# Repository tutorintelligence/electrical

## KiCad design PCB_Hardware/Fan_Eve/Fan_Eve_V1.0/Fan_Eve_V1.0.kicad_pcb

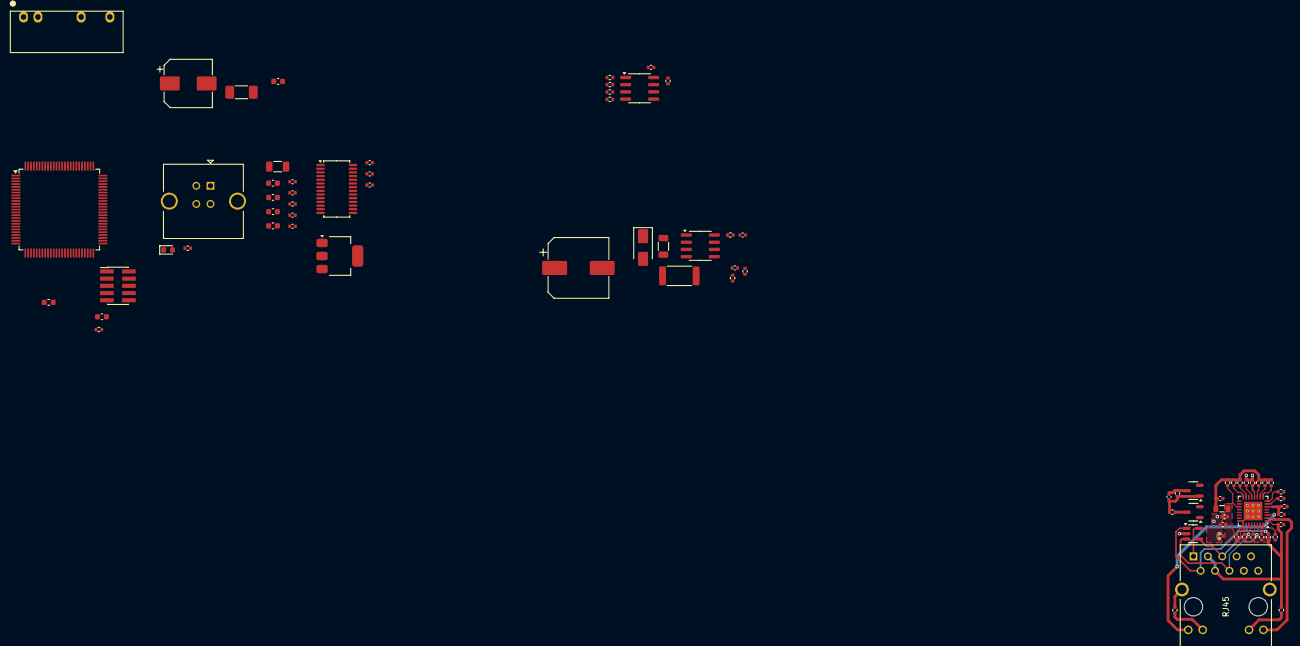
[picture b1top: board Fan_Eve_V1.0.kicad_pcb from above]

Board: 4 copper layers, 78 parts (0 on the bottom side), 56 nets.

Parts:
C1: 4.7u; C_0603_1608Metric
C2, C3, C4, C5, C6, C7, C9, C11, C14, C17, C18, C20, C21, C22, C24, C30, C31: 100n; C_0402_1005Metric
C8, C10: 1u; C_0402_1005Metric
C12, C13, C15, C28: 22u; C_0603_1608Metric
C16: 1n; C_1206_3216Metric
C19: 2.2u; C_0603_1608Metric
C23: 15u; CP_Elec_10x10.5
C25: 10p; C_0402_1005Metric
C26: 470u; CP_Elec_8x10
C27: 1n; C_1808_4520Metric
C29: 10u; C_0402_1005Metric
D2: SS510; D_SMA
D3: LED; LED_0603_1608Metric
FB1: FerriteBead; L_0603_1608Metric
J1: Conn_ARM_JTAG_SWD_10; PinHeader_2x05_P1.27mm_Vertical_SMD
J2: USB_B; USB_B_TE_5787834_Vertical
L1: FB0805/600R/2A; L_0805_2012Metric
Q1: WPM2015-3/TR; SOT-23-3
Q2: LMUN2211LT1G; SOT-23-3
R1, R2, R16, R20: 10k; R_0402_1005Metric
R3: 1k; R_0402_1005Metric
R4, R5, R6, R7: 49.9; R_0402_1005Metric
R8, R9, R10, R11, R12, R13, R14, R15, R17, R18, R30: 2.2k; R_0402_1005Metric
R19: 12.1k; R_0402_1005Metric
R21: 130k; R_0402_1005Metric
R22: 4.42k; R_0402_1005Metric
R23: 180k; R_0402_1005Metric
R24: 24.9k; R_0402_1005Metric
R25: 30m; R_1206_3216Metric
R26: 4.7k; R_2512_6332Metric
R27: 4.7; R_0402_1005Metric
R28: 56.2k; R_0402_1005Metric
R29: 10.5k; R_0402_1005Metric
RJ1: HY931147C
U1: STM32H743VITx; LQFP-100_14x14mm_P0.5mm
U2: LAN8710A-EZC; QFN-32-1EP_5x5mm_P0.5mm_EP3.3x3.3mm_ThermalVias
U3: ESDS314DBVR; SOT-23-5
U4: TPS2376D; SOIC-8_3.9x4.9mm_P1.27mm
U5: TX4138; SOIC-8_3.9x4.9mm_P1.27mm
U6: F0505S-2WR2
U7: AMS1117-3.3; SOT-223-3_TabPin2
U8: PCA9685PW; TSSOP-28_4.4x9.7mm_P0.65mm

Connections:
+3.3V: C1.1, C2.1, C3.1, C4.1, C5.1, C6.1, C7.1, C10.1, C12.1, FB1.2, J1.1 (VTref), Q1.3 (D), R2.1, U1.6 (VBAT), U1.11 (VDD), U1.27 (VDD), U1.50 (VDD), U1.75 (VDD), U1.100 (VDD)
+3.3VA: C8.1, C9.1, FB1.1, U1.21 (VDDA)
+3.3VLAN: C13.1, C14.1, L1.1, Q1.2 (S), R8.2, R9.2, R10.2, R14.2, R15.2, R16.2, U2.12 (VDDIO)
+5V: C28.2, C29.1, C30.1, U6.5 (0V), U8.1 (A0), U8.3 (A2), U8.5 (A4), U8.28 (VDD)
+5V USB: D3.2 (A), J2.1 (VBUS)
/Ethernet/ETHGREEN: RJ1.P$14 (G-), U2.2 (LED2/~INTSEL)
/Ethernet/ETHYELLOW: RJ1.P$11 (Y+), U2.3 (LED1/~REGOFF)
/Ethernet/ETH_CRS_DV: R14.1, U1.31 (PA7), U2.15 (COL/CRS_DV/~MODE2)
/Ethernet/ETH_MDC: U1.16 (PC1), U2.17 (MDC)
/Ethernet/ETH_MDIO: R15.1, U1.24 (PA2), U2.16 (MDIO)
/Ethernet/ETH_REF_CLK: U1.23 (PA1), U2.5 (XTAL1/CLKIN)
/Ethernet/ETH_RXD0: R8.1, U1.32 (PC4), U2.11 (RXD0/~MODE0)
/Ethernet/ETH_RXD1: R9.1, U1.33 (PC5), U2.10 (RXD1/~MODE1)
/Ethernet/ETH_TXD0: U1.51 (PB12), U2.22 (TXD0)
/Ethernet/ETH_TXD1: U1.52 (PB13), U2.23 (TXD1)
/Ethernet/ETH_TX_EN: U1.47 (PB11), U2.21 (TXEN)
/Ethernet/V+: C22.1, C23.1, R21.1, R24.1, R25.1, R26.1, RJ1.P$9 (V+), U4.8 (VDD), U5.3 (VIN)
/Ethernet/V-: C22.2, R20.1, R22.1, R23.1, RJ1.P$10 (V-), U4.4 (VSS)
/MCU/NRST: C11.1, U1.14 (NRST)
/MCU/SWCLK: J1.4 (SWCLK/TCK), U1.76 (PA14)
/MCU/SWDIO: J1.2 (SWDIO/TMS), U1.72 (PA13)
/MCU/SWO: J1.6 (SWO/TDO), U1.89 (PB3)
/MCU/USB_D+: J2.3 (D+), U1.71 (PA12)
/MCU/USB_D-: J2.2 (D-), U1.70 (PA11)
/POE/ILIM: R25.2, U5.2 (ILIM_1)
/POE/POE_EN: U4.6 (PG), U5.6 (EN)
GND: C1.2, C2.2, C3.2, C4.2, C5.2, C6.2, C7.2, C8.2, C9.2, C10.2, C11.2, C13.2, C14.2, C15.2, C16.2, C17.2, C18.2, C19.1, C20.1, C21.1, C27.1, C28.1, C29.2, C30.2, C31.2, J1.3 (GND), J1.5 (GND), J1.9 (GNDDetect), J2.4 (GND), J2.5 (Shield), Q2.2 (E), R1.2, R11.1, R12.1, R13.1, R18.2, R19.1, R30.2, RJ1.GND1, RJ1.GND2, U1.10 (VSS), U1.19 (VSSA), U1.26 (VSS), U1.49 (VSS), U1.74 (VSS), U1.99 (VSS), U2.24 (TXD2), U2.25 (TXD3), U2.33 (VSS), U3.2 (GND), U6.7 (+Vo), U8.2 (A1), U8.4 (A3), U8.14 (VSS), U8.24 (A5)
GNDPWR: C23.2, C26.2, C27.2, D2.2 (A), R26.2, R29.1, U4.5 (RTN), U5.4 (GND), U6.2 (GND)
unnamed: C24.1, R27.2
unnamed: C24.2, D2.1 (K), U5.1 (SW)
unnamed: D3.1 (K), R30.1
unnamed: C12.2, Q1.1 (G), R2.2, R3.1
unnamed: Q2.3 (C), R3.2
unnamed: R17.1, RJ1.P$13 (G+)
unnamed: R7.2, RJ1.P$1 (RX+), U2.30 (RXN), U3.5 (I/O4)
unnamed: R6.2, RJ1.P$2 (RX-), U2.31 (RXP), U3.1 (I/O1)
unnamed: C15.1, C16.1, C17.1, C18.1, C21.2, L1.2, R4.1, R5.1, R6.1, R7.1, R17.2, RJ1.P$3 (RXCT), RJ1.P$4 (TXCT), U2.1 (VDD2A), U2.27 (VDD1A)
unnamed: R5.2, RJ1.P$5 (TX+), U2.28 (TXN), U3.4 (I/O3)
unnamed: R4.2, RJ1.P$6 (TX-), U2.29 (TXP), U3.3 (I/O2)
unnamed: R18.1, RJ1.P$12 (Y-)
unnamed: R1.1, U1.94 (BOOT0)
unnamed: R19.2, U2.32 (RBIAS)
unnamed: R12.2, U2.7 (RXCLK/~PHYAD1)
unnamed: R10.1, U2.9 (RXD2/~RMIISEL)
unnamed: R11.2, U2.8 (RXD3/~PHYAD2)
unnamed: R13.2, U2.13 (RXER/RXD4/~PHYAD0)
unnamed: C19.2, C20.2, U2.6 (VDDCR)
unnamed: R16.1, U2.19 (~RST)
unnamed: R22.2, U4.2 (CLASS)
unnamed: R24.2, U4.3 (DET)
unnamed: R23.2, U4.1 (ILIM)
unnamed: R20.2, R21.2, U4.7 (UVLO)
unnamed: R27.1, U5.8 (BS)
unnamed: C25.1, R28.1, R29.2, U5.5 (FB)
unnamed: C25.2, C26.1, R28.2, U6.1 (Vin)
unnamed: C31.1, U8.25 (EXTCLK)

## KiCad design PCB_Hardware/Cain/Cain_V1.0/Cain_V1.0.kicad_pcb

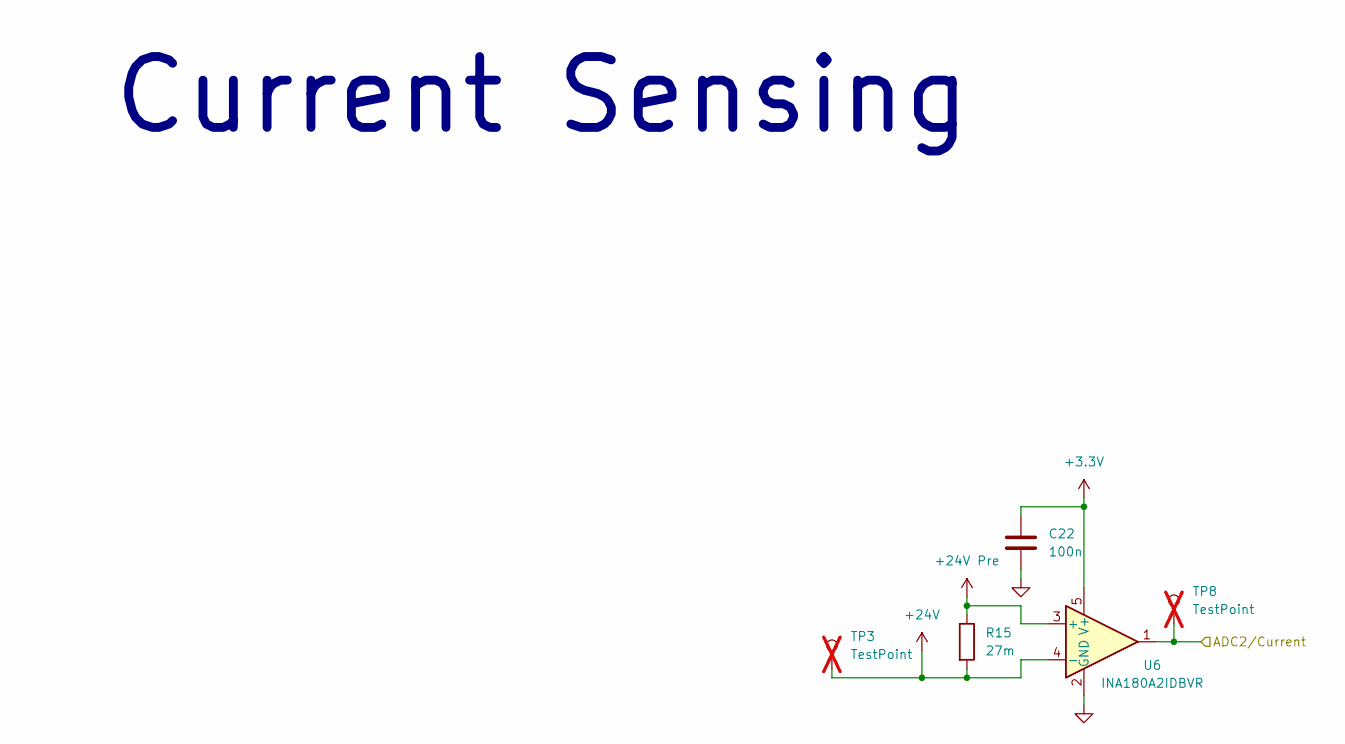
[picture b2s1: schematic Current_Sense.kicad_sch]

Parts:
C22: 100n; C_0402_1005Metric; JLCPCB Part Number C1525
R15: 27m; R_1206_3216Metric; JLCPCB Part Number C2988658
TP3, TP8: TestPoint; TestPoint_Pad_D1.0mm; not fitted
U6: INA180A2IDBVR; SOT-23-5; JLCPCB Part Number C192764

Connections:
+3.3V: C22.1, U6.5 (V+); also elsewhere on the board
+24V: R15.2, TP3.1, U6.4 (-); also elsewhere on the board
+24V Pre: R15.1, U6.3 (+); also elsewhere on the board
/Current Sense/ADC2/Current: TP8.1, U6.1; also elsewhere on the board
GND: C22.2, U6.2 (GND); also elsewhere on the board

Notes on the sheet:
Current Sensing

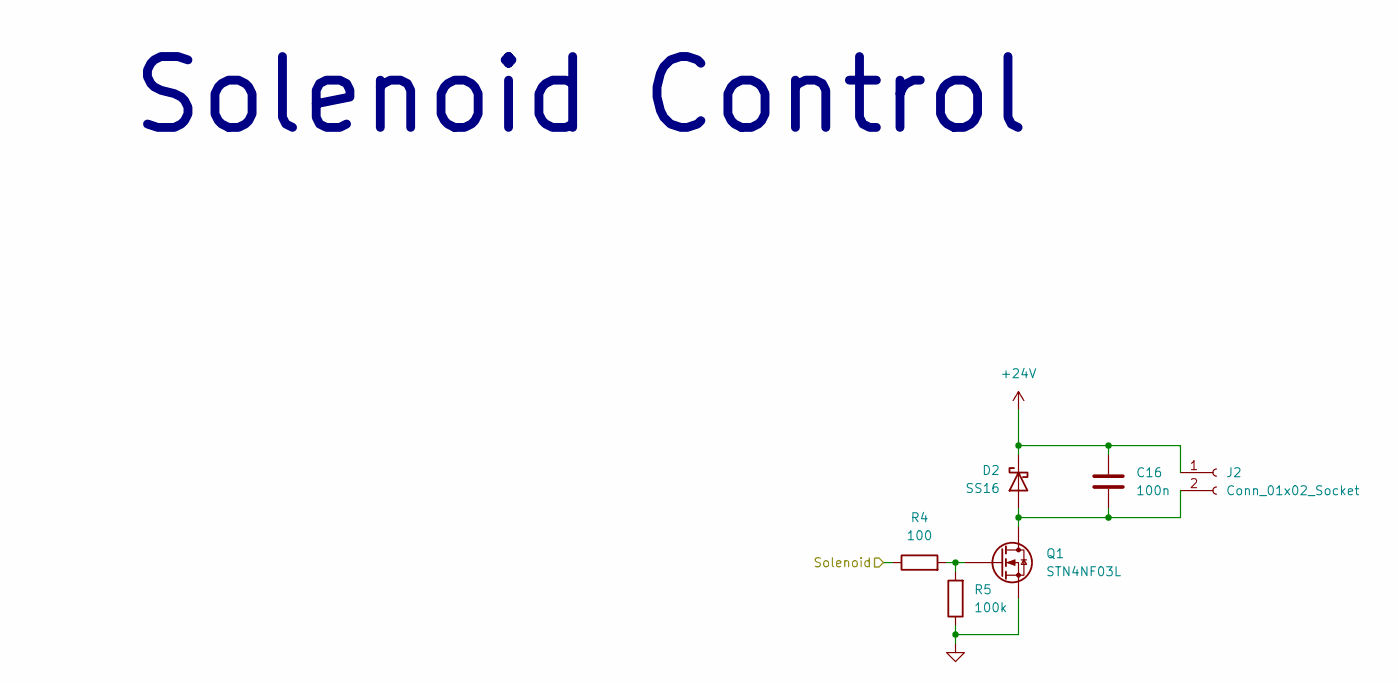
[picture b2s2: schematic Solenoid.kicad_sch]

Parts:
C16: 100n; C_0603_1608Metric; JLCPCB Part Number C1591
D2: SS16; D_SMA; JLCPCB Part Number C557917
J2: Conn_01x02_Socket; JST_XH_B2B-XH-A_1x02_P2.50mm_Vertical; JLCPCB Part Number C158012
Q1: STN4NF03L; SOT-223-3_TabPin2; JLCPCB Part Number C85568
R4: 100; R_0402_1005Metric; JLCPCB Part Number C25076
R5: 100k; R_0402_1005Metric; JLCPCB Part Number C25741

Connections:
+24V: C16.1, D2.1 (K), J2.1; also elsewhere on the board
/MCU/Solenoid: R4.1; also elsewhere on the board
GND: Q1.3 (S), R5.1; also elsewhere on the board
unnamed: C16.2, D2.2 (A), J2.2, Q1.2 (D)
unnamed: Q1.1 (G), R4.2, R5.2

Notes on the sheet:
Solenoid Control

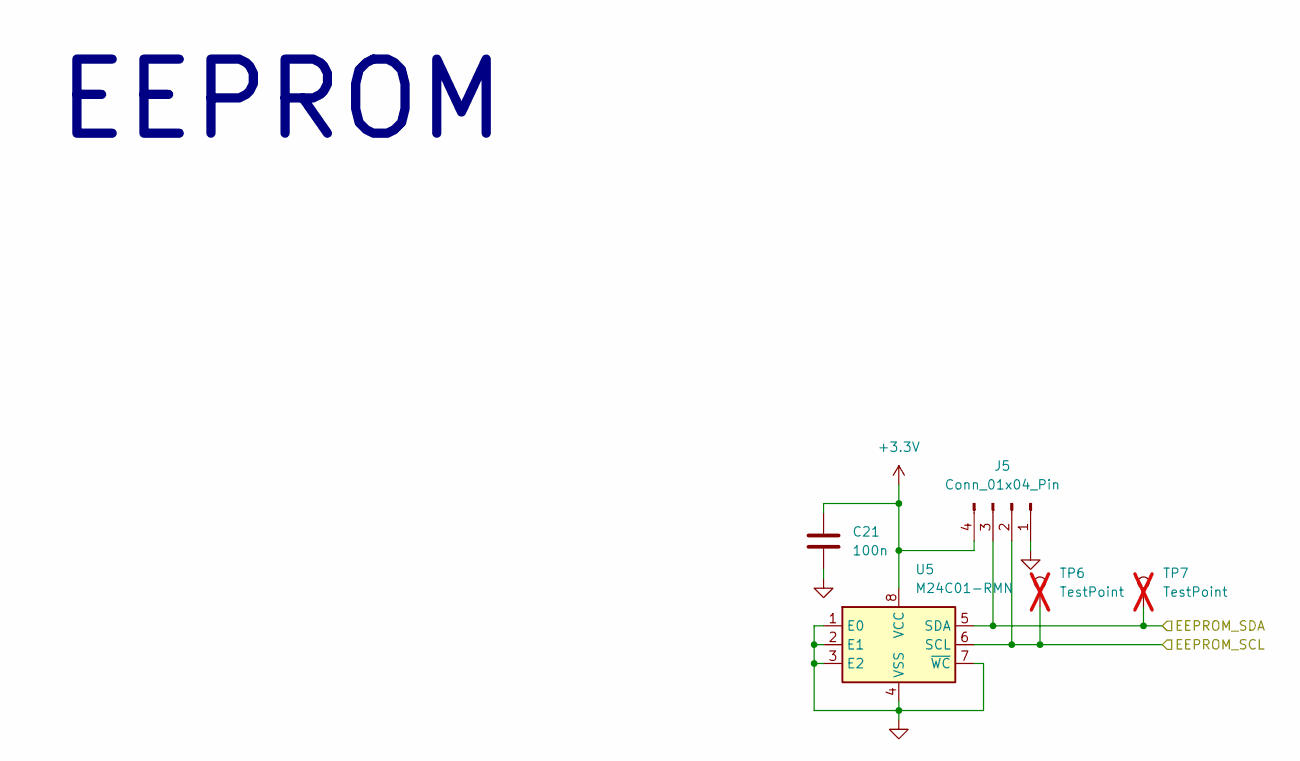
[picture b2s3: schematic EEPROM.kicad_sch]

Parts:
C21: 100n; C_0402_1005Metric; JLCPCB Part Number C1525
J5: Conn_01x04_Pin; PinHeader_1x04_P1.00mm_Vertical; JLCPCB Part Number C37328854
TP6, TP7: TestPoint; TestPoint_Pad_D1.0mm; not fitted
U5: M24C01-RMN; SOIC-8_3.9x4.9mm_P1.27mm; JLCPCB Part Number C146163

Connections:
+3.3V: C21.1, J5.4, U5.8 (VCC); also elsewhere on the board
/EEPROM/EEPROM_SCL: J5.2, TP6.1, U5.6 (SCL); also elsewhere on the board
/EEPROM/EEPROM_SDA: J5.3, TP7.1, U5.5 (SDA); also elsewhere on the board
GND: C21.2, J5.1, U5.1 (E0), U5.2 (E1), U5.3 (E2), U5.4 (VSS), U5.7 (~WC); also elsewhere on the board

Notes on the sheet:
EEPROM

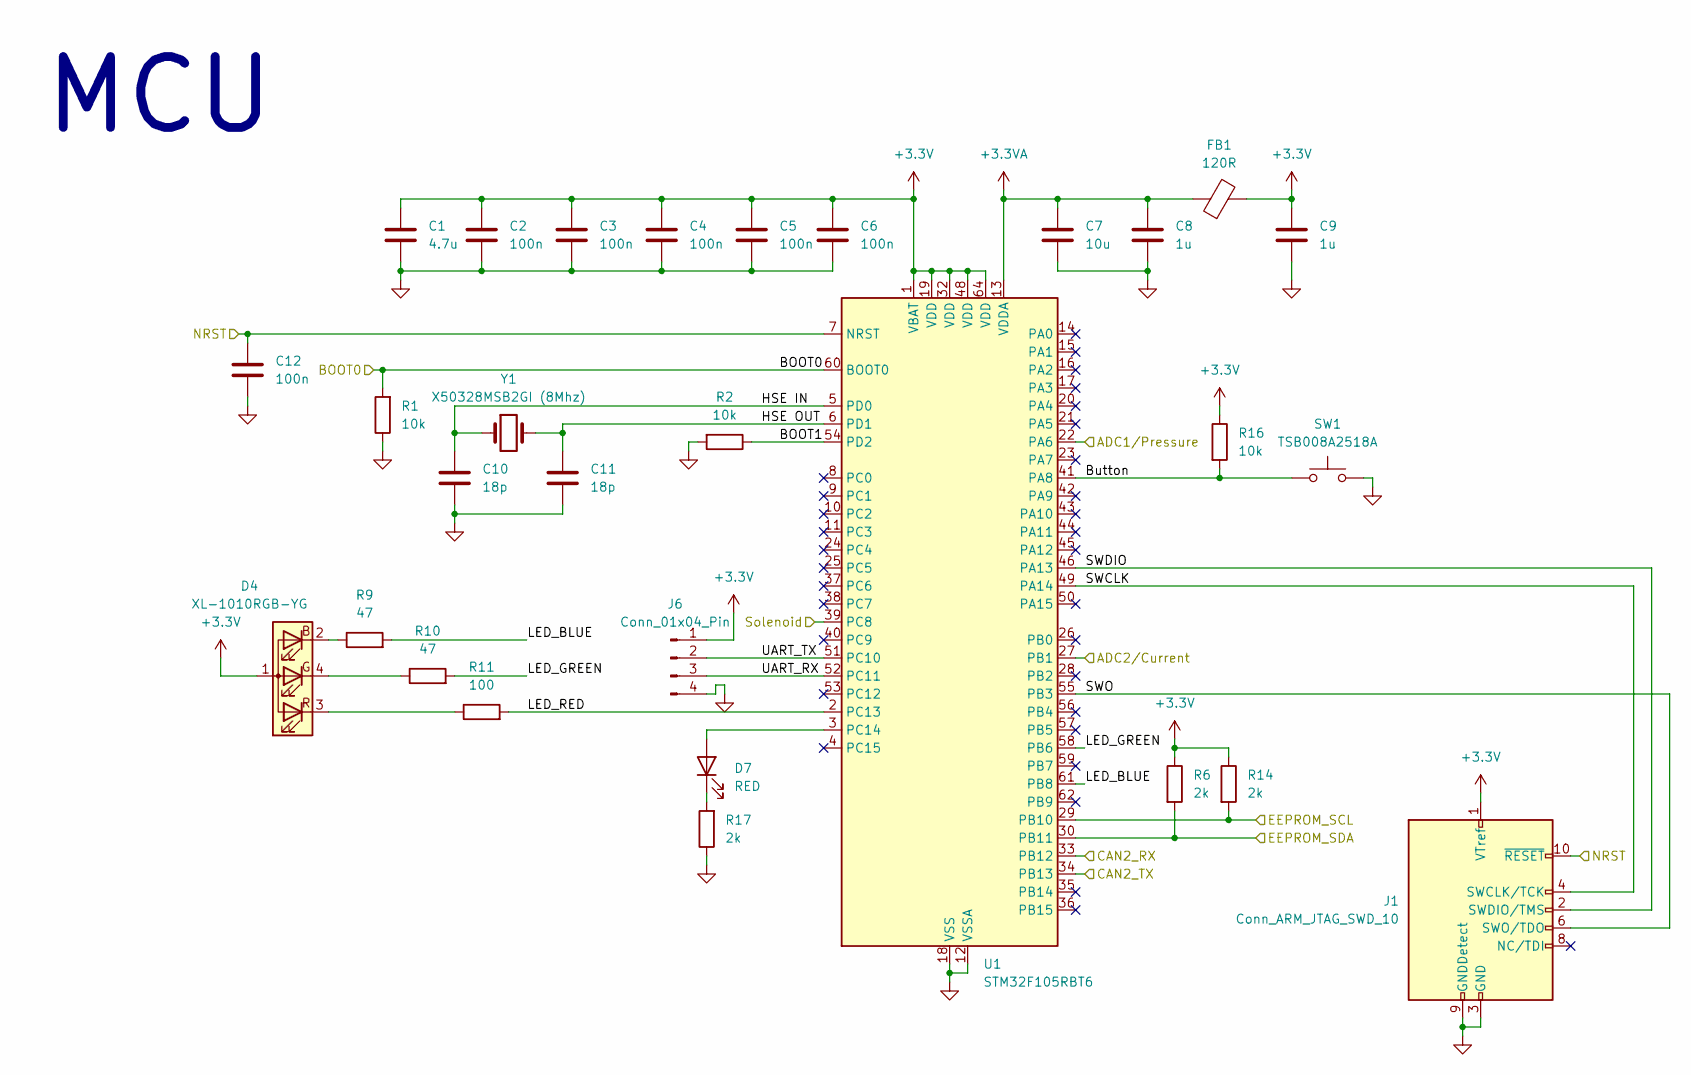
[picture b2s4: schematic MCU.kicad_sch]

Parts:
C1: 4.7u; C_0603_1608Metric; JLCPCB Part Number C19666
C2, C3, C4, C5, C6, C12: 100n; C_0402_1005Metric; JLCPCB Part Number C1525
C7: 10u; C_0402_1005Metric; JLCPCB Part Number C15525
C8, C9: 1u; C_0402_1005Metric; JLCPCB Part Number C1525
C10, C11: 18p; C_0402_1005Metric; JLCPCB Part Number C52923
D4: XL-1010RGB-YG; LED_01x01; JLCPCB Part Number C965834
D7: RED; LED_0603_1608Metric; JLCPCB Part Number C434419
FB1: 120R; L_0603_1608Metric; JLCPCB Part Number C113030
J1: Conn_ARM_JTAG_SWD_10; PinHeader_2x05_P1.27mm_Vertical; JLCPCB Part Number C2935953
J6: Conn_01x04_Pin; PinHeader_1x04_P1.00mm_Vertical; JLCPCB Part Number C37328854
R1, R2, R16: 10k; R_0402_1005Metric; JLCPCB Part Number C25744
R6, R14, R17: 2k; R_0402_1005Metric; JLCPCB Part Number C4109
R9, R10: 47; R_0402_1005Metric; JLCPCB Part Number C1211
R11: 100; R_0402_1005Metric; JLCPCB Part Number C25076
SW1: TSB008A2518A; JLCPCB Part Number C2888455
U1: STM32F105RBT6; LQFP-64_10x10mm_P0.5mm; JLCPCB Part Number C8349
Y1: X50328MSB2GI (8Mhz); Crystal_SMD_5032-2Pin_5.0x3.2mm; JLCPCB Part Number C115962

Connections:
+3.3V: C1.1, C2.1, C3.1, C4.1, C5.1, C6.1, C9.1, D4.1 (A), FB1.2, J1.1 (VTref), J6.1, R6.1, R14.1, R16.1, U1.1 (VBAT), U1.19 (VDD), U1.32 (VDD), U1.48 (VDD), U1.64 (VDD); also elsewhere on the board
+3.3VA: C7.1, C8.1, FB1.1, U1.13 (VDDA); also elsewhere on the board
/CAN2.0/Power/CAN2_RX: U1.33 (PB12); also elsewhere on the board
/CAN2.0/Power/CAN2_TX: U1.34 (PB13); also elsewhere on the board
/CAN2.0/Power/NRST: C12.1, J1.10 (~RESET), U1.7 (NRST); also elsewhere on the board
/Current Sense/ADC2/Current: U1.27 (PB1); also elsewhere on the board
/EEPROM/EEPROM_SCL: R14.2, U1.29 (PB10); also elsewhere on the board
/EEPROM/EEPROM_SDA: R6.2, U1.30 (PB11); also elsewhere on the board
/MCU/ADC1/Pressure: U1.22 (PA6); also elsewhere on the board
/MCU/BOOT0: R1.2, U1.60 (BOOT0); also elsewhere on the board
/MCU/BOOT1: R2.1, U1.54 (PD2)
/MCU/Button: R16.2, SW1.1, U1.41 (PA8)
/MCU/HSE IN: C10.1, U1.5 (PD0), Y1.1
/MCU/HSE OUT: C11.1, U1.6 (PD1), Y1.2
/MCU/LED_BLUE: R9.2, U1.61 (PB8)
/MCU/LED_GREEN: R10.2, U1.58 (PB6)
/MCU/LED_RED: R11.2, U1.2 (PC13)
/MCU/SWCLK: J1.4 (SWCLK/TCK), U1.49 (PA14)
/MCU/SWDIO: J1.2 (SWDIO/TMS), U1.46 (PA13)
/MCU/SWO: J1.6 (SWO/TDO), U1.55 (PB3)
/MCU/Solenoid: U1.39 (PC8); also elsewhere on the board
/MCU/UART_RX: J6.3, U1.52 (PC11)
/MCU/UART_TX: J6.2, U1.51 (PC10)
GND: C1.2, C2.2, C3.2, C4.2, C5.2, C6.2, C7.2, C8.2, C9.2, C10.2, C11.2, C12.2, J1.3 (GND), J1.5 (GND), J1.9 (GNDDetect), J6.4, R1.1, R2.2, R17.1, SW1.2, U1.12 (VSSA), U1.18 (VSS), U1.31 (VSS), U1.47 (VSS), U1.63 (VSS); also elsewhere on the board
unnamed: D4.2 (BK), R9.1
unnamed: D4.4 (GK), R10.1
unnamed: D4.3 (RK), R11.1
unnamed: D7.2 (A), U1.3 (PC14)
unnamed: D7.1 (K), R17.2

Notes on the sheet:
MCU

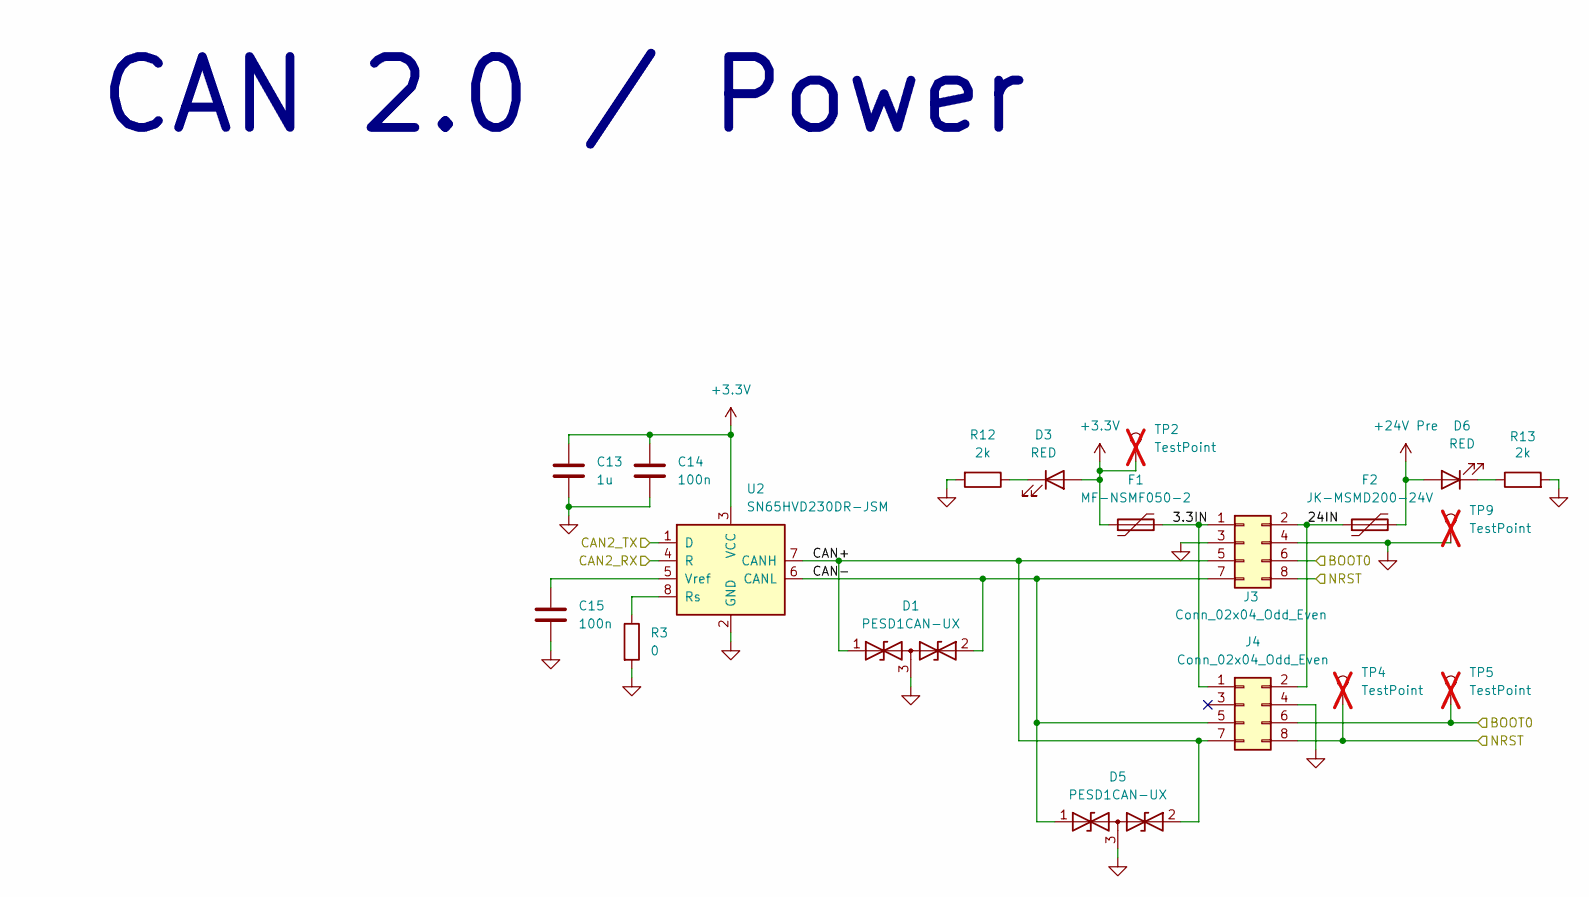
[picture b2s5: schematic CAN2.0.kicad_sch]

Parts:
C13: 1u; C_0402_1005Metric; JLCPCB Part Number C1525
C14, C15: 100n; C_0402_1005Metric; JLCPCB Part Number C1525
D1, D5: PESD1CAN-UX; SOT-323_SC-70; JLCPCB Part Number C152727
D3, D6: RED; LED_0603_1608Metric; JLCPCB Part Number C434419
F1: MF-NSMF050-2; Fuse_1210_3225Metric; JLCPCB Part Number C75464
F2: JK-MSMD200-24V; Fuse_1812_4532Metric; JLCPCB Part Number C561584
J3, J4: Conn_02x04_Odd_Even; CONN_B8B-PHDSS_JST; JLCPCB Part Number C157975
R3: 0; R_0402_1005Metric; JLCPCB Part Number C1091
R12, R13: 2k; R_0402_1005Metric; JLCPCB Part Number C4109
TP2, TP4, TP5, TP9: TestPoint; TestPoint_Pad_D1.0mm; not fitted
U2: SN65HVD230DR-JSM; SOIC-8_3.9x4.9mm_P1.27mm; JLCPCB Part Number C46596299

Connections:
+3.3V: C13.1, C14.1, D3.2 (A), F1.1, TP2.1, U2.3 (VCC); also elsewhere on the board
+24V Pre: D6.2 (A), F2.2; also elsewhere on the board
/CAN2.0/Power/3.3IN: F1.2, J3.1, J4.1
/CAN2.0/Power/24IN: F2.1, J3.2, J4.2
/CAN2.0/Power/CAN2_RX: U2.4 (R); also elsewhere on the board
/CAN2.0/Power/CAN2_TX: U2.1 (D); also elsewhere on the board
/CAN2.0/Power/CAN+: D1.1 (A1), D5.2 (A2), J3.5, J4.7, U2.7 (CANH)
/CAN2.0/Power/CAN-: D1.2 (A2), D5.1 (A1), J3.7, J4.5, U2.6 (CANL)
/CAN2.0/Power/NRST: J3.8, J4.8, TP4.1; also elsewhere on the board
/MCU/BOOT0: J3.6, J4.6, TP5.1; also elsewhere on the board
GND: C13.2, C14.2, C15.2, D1.3 (common), D5.3 (common), J3.3, J3.4, J4.4, R3.2, R12.2, R13.2, TP9.1, U2.2 (GND); also elsewhere on the board
unnamed: D3.1 (K), R12.1
unnamed: D6.1 (K), R13.1
unnamed: R3.1, U2.8 (Rs)
unnamed: C15.1, U2.5 (Vref)

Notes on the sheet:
CAN 2.0 / Power

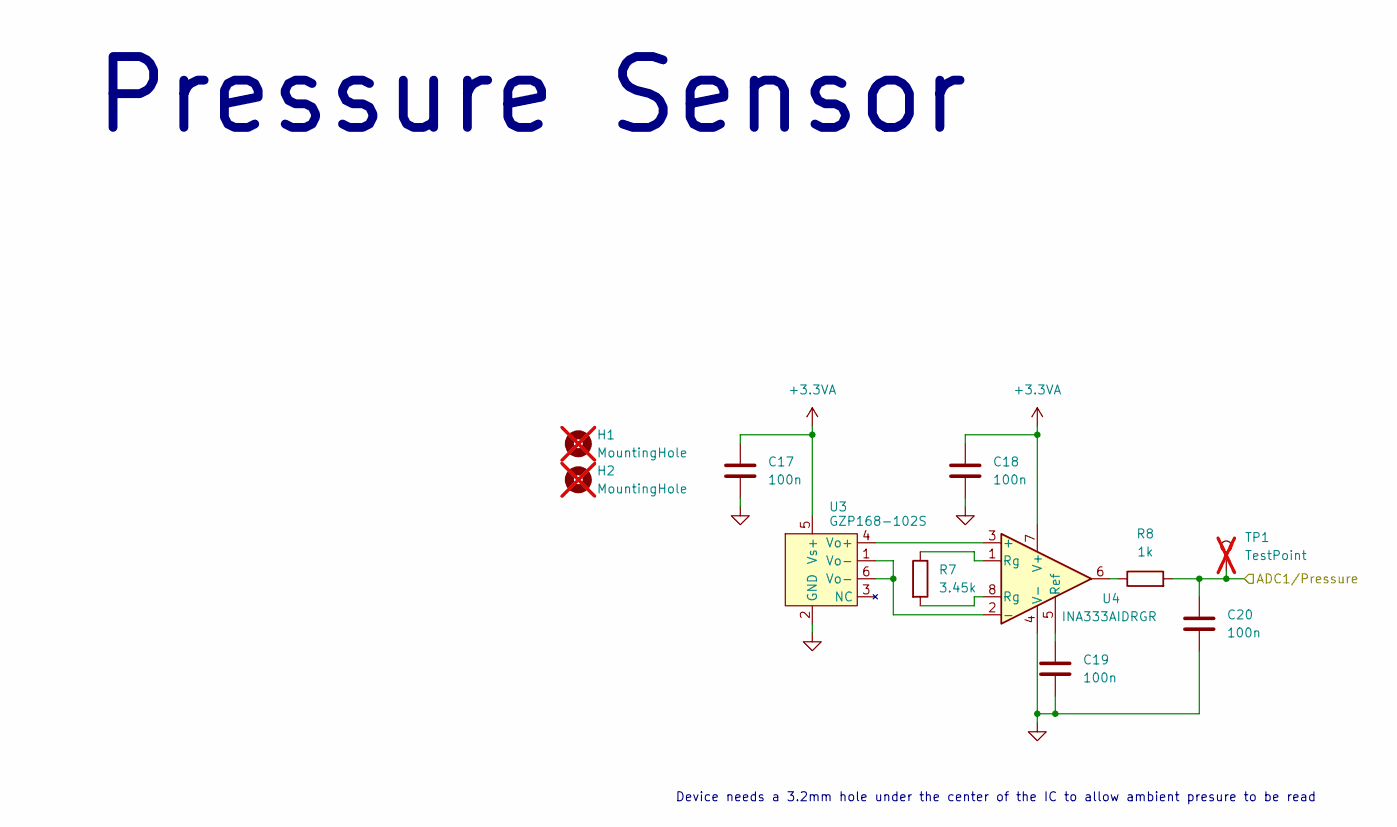
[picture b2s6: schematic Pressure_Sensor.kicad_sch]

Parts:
C17, C18, C19, C20: 100n; C_0402_1005Metric; JLCPCB Part Number C1525
H1, H2: MountingHole; MountingHole_3.2mm_M3; not fitted
R7: 3.45k; R_0402_1005Metric; JLCPCB Part Number C4940
R8: 1k; R_0402_1005Metric; JLCPCB Part Number C11702
TP1: TestPoint; TestPoint_Pad_D1.0mm; not fitted
U3: GZP168-102S; JLCPCB Part Number C3037990
U4: INA333AIDRGR; VSSOP-8_3x3mm_P0.65mm; JLCPCB Part Number C2057429

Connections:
+3.3VA: C17.1, C18.1, U3.5 (Vs+), U4.7 (V+); also elsewhere on the board
/MCU/ADC1/Pressure: C20.1, R8.2, TP1.1; also elsewhere on the board
GND: C17.2, C18.2, C19.2, C20.2, U3.2 (GND), U4.4 (V-); also elsewhere on the board
unnamed: R7.1, U4.1 (Rg)
unnamed: R7.2, U4.8 (Rg)
unnamed: R8.1, U4.6
unnamed: U3.4 (Vo+), U4.3 (+)
unnamed: U3.1 (Vo-), U3.6 (Vo-), U4.2 (-)
unnamed: C19.1, U4.5 (Ref)

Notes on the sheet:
Device needs a 3.2mm hole under the center of the IC to allow ambient presure to be read
Pressure Sensor

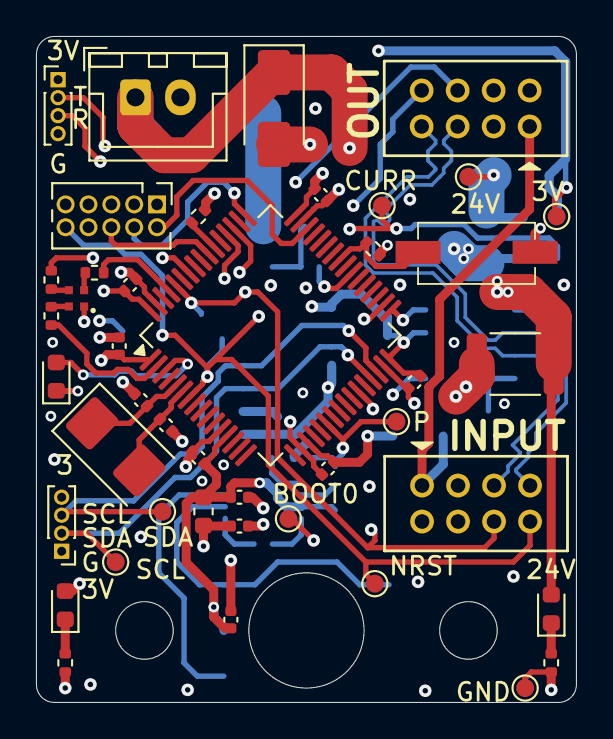
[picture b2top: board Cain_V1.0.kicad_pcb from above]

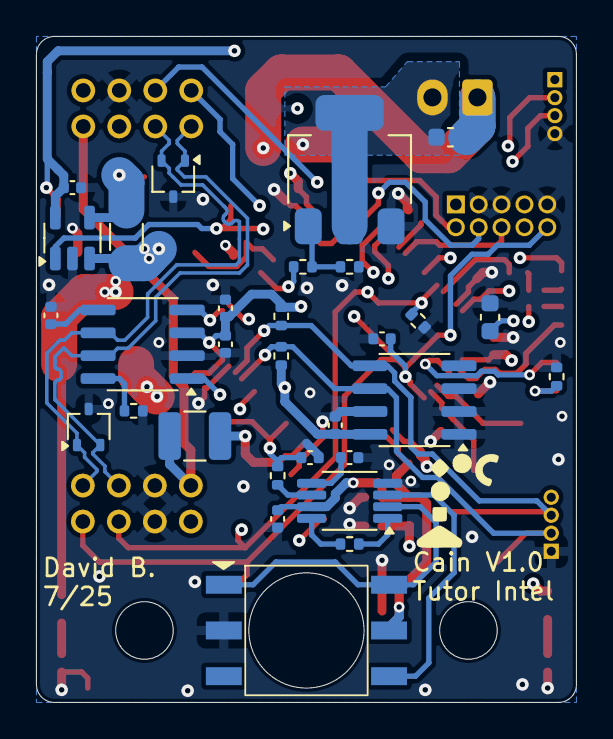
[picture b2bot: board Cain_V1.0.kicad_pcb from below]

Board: 4 copper layers, 30.0 x 37.0 mm, 75 parts (30 on the bottom side), 47 nets.

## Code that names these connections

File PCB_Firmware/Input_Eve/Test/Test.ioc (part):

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Mcu.Name=STM32H743ZITx
Mcu.Package=LQFP144
Mcu.UserName=STM32H743ZITx
PA1.Mode=RMII
PA1.Signal=ETH_REF_CLK
PA10.Signal=S_TIM1_CH3
PA11.Mode=Device_Only
PA11.Signal=USB_OTG_FS_DM
PA12.Mode=Device_Only
PA12.Signal=USB_OTG_FS_DP
PA13\ (JTMS/SWDIO).Mode=Trace_Asynchronous_SW
PA13\ (JTMS/SWDIO).Signal=DEBUG_JTMS-SWDIO
PA14\ (JTCK/SWCLK).Mode=Trace_Asynchronous_SW
PA14\ (JTCK/SWCLK).Signal=DEBUG_JTCK-SWCLK
PA15\ (JTDI).Mode=Hardware Flow Control (RS485)
PA15\ (JTDI).Signal=UART4_DE
PA2.Mode=RMII
PA2.Signal=ETH_MDIO
PA3.Signal=ADCx_INP15
PA4.Signal=ADCx_INP18
PA5.Signal=ADCx_INP19
PA6.Signal=ADCx_INP3
PA7.Mode=RMII
PA7.Signal=ETH_CRS_DV
PA8.Signal=S_TIM1_CH1
PA9.Mode=Activate_VBUS
PA9.Signal=USB_OTG_FS_VBUS
PB0.Signal=ADCx_INP9
PB1.Signal=ADCx_INP5
PB10.Signal=S_TIM2_CH3
PB11.Mode=RMII
PB11.Signal=ETH_TX_EN
PB12.GPIOParameters=GPIO_Label
PB12.GPIO_Label=USB_FAULT
PB12.Signal=GPIO_Input
PB13.Mode=Activate_VBUS_FS
PB13.Signal=USB_OTG_HS_VBUS
PB14.Mode=Host_FS
PB14.Signal=USB_OTG_HS_DM
PB15.Mode=Host_FS
PB15.Signal=USB_OTG_HS_DP
PB2.Mode=Single Bank 2
PB2.Signal=QUADSPI_CLK
PB3\ (JTDO/TRACESWO).Mode=Trace_Asynchronous_SW
PB3\ (JTDO/TRACESWO).Signal=DEBUG_JTDO-SWO
PB4\ (NJTRST).Signal=S_TIM3_CH1
PB5.Signal=S_TIM3_CH2
PB6.Signal=S_TIM4_CH1
PB7.Signal=S_TIM4_CH2
PB8.Signal=S_TIM4_CH3
PB9.Signal=S_TIM4_CH4
PC0.Signal=ADCx_INP10
PC1.Mode=RMII
PC1.Signal=ETH_MDC
PC10.GPIOParameters=GPIO_Label
PC10.GPIO_Label=RS485_TX
PC10.Mode=Asynchronous
PC10.Signal=UART4_TX
PC11.Mode=Single Bank 2
PC11.Signal=QUADSPI_BK2_NCS
PC12.GPIOParameters=GPIO_Label
PC12.GPIO_Label=RS232_TX_1
PC12.Mode=Asynchronous
PC12.Signal=UART5_TX
PC14-OSC32_IN\ (OSC32_IN).Mode=LSE-External-Oscillator
PC14-OSC32_IN\ (OSC32_IN).Signal=RCC_OSC32_IN
PC15-OSC32_OUT\ (OSC32_OUT).Mode=LSE-External-Oscillator
PC15-OSC32_OUT\ (OSC32_OUT).Signal=RCC_OSC32_OUT
PC2_C.Mode=IN0-Single-Ended
PC2_C.Signal=ADC3_INP0
PC3_C.Mode=IN1-Single-Ended
PC3_C.Signal=ADC3_INP1
PC4.Mode=RMII
PC4.Signal=ETH_RXD0
PC5.Mode=RMII
PC5.Signal=ETH_RXD1
PC6.Signal=S_TIM8_CH1
PC7.Signal=S_TIM8_CH2
PC8.Signal=S_TIM8_CH3
PC9.Signal=S_TIM8_CH4
PD0.GPIOParameters=GPIO_Label
PD0.GPIO_Label=RS485_RX
PD0.Mode=Asynchronous
PD0.Signal=UART4_RX
PD10.Signal=S_CKOUTDFSDM1
PD11.GPIOParameters=GPIO_Label
PD11.GPIO_Label=SEL
PD11.Signal=GPIO_Input
PD12.Mode=I2C
PD12.Signal=I2C4_SCL
PD13.Mode=I2C
PD13.Signal=I2C4_SDA
PD2.GPIOParameters=GPIO_Label
PD2.GPIO_Label=RS232_RX_1
PD2.Mode=Asynchronous
PD2.Signal=UART5_RX
PD5.Mode=Asynchronous
PD5.Signal=USART2_TX
PD6.Mode=Asynchronous
PD6.Signal=USART2_RX
PD8.GPIOParameters=GPIO_Label
PD8.GPIO_Label=USB_EN
PD8.Signal=GPIO_Output
PD9.Signal=S_DATAIN3DFSDM1
PE0.Mode=Asynchronous
PE0.Signal=UART8_RX
PE1.Mode=Asynchronous
PE1.Signal=UART8_TX
PE10.Signal=GPIO_Input
PE11.GPIOParameters=GPIO_Label
PE11.GPIO_Label=TPL
PE11.Signal=GPIO_Input
PE12.GPIOParameters=GPIO_Label
PE12.GPIO_Label=BT
PE12.Signal=GPIO_Input
PE14.Signal=S_TIM1_CH4
PE2.Mode=Full_Duplex_Master
PE2.Signal=SPI4_SCK
PE3.Signal=GPIO_Output
PE4.GPIOParameters=GPIO_Label
PE4.GPIO_Label=HOLD
PE4.Signal=GPIO_Output
PE5.Mode=Full_Duplex_Master
PE5.Signal=SPI4_MISO
PE6.Mode=Full_Duplex_Master
PE6.Signal=SPI4_MOSI
PE7.Mode=Single Bank 2
PE7.Signal=QUADSPI_BK2_IO0
PE8.Mode=Single Bank 2
PE8.Signal=QUADSPI_BK2_IO1
PE9.GPIOParameters=GPIO_Label
PE9.GPIO_Label=Temp_ALERT
PE9.Signal=GPXTI9
PF10.Mode=IN6-Single-Ended
PF10.Signal=ADC3_INP6
PF11.Mode=IN2-Single-Ended
PF11.Signal=ADC1_INP2
PF12.Mode=IN6-Single-Ended
PF12.Signal=ADC1_INP6
PF13.Mode=IN2-Single-Ended
PF13.Signal=ADC2_INP2
PF14.Mode=IN6-Single-Ended
PF14.Signal=ADC2_INP6
PF15.GPIOParameters=GPIO_Label
PF15.GPIO_Label=ETH_INT
PF15.Signal=GPXTI15
PF3.Mode=IN5-Single-Ended
PF3.Signal=ADC3_INP5
PF4.Mode=IN9-Single-Ended
PF4.Signal=ADC3_INP9
PF5.Mode=IN4-Single-Ended
PF5.Signal=ADC3_INP4
PF6.Mode=IN8-Single-Ended
PF6.Signal=ADC3_INP8
PF7.Signal=S_TIM17_CH1
PF8.Mode=IN7-Single-Ended
PF8.Signal=ADC3_INP7
PF9.Mode=IN2-Single-Ended
PF9.Signal=ADC3_INP2
PG0.GPIOParameters=GPIO_Label
PG0.GPIO_Label=Input_Curr_INT
PG0.Signal=GPXTI0
PG10.GPIOParameters=GPIO_Label
PG10.GPIO_Label=IMU_INT_1
PG10.Signal=GPXTI10
PG11.GPIOParameters=GPIO_Label
PG11.GPIO_Label=IMU_INT_2
PG11.Signal=GPXTI11
PG12.Mode=RMII
PG12.Signal=ETH_TXD1
PG13.Mode=RMII
PG13.Signal=ETH_TXD0
PG14.Mode=Single Bank 2
PG14.Signal=QUADSPI_BK2_IO3
PG15.GPIOParameters=GPIO_Label
PG15.GPIO_Label=CS_IMU
PG15.Signal=GPIO_Output
PG9.Mode=Single Bank 2
PG9.Signal=QUADSPI_BK2_IO2
PH0-OSC_IN\ (PH0).Mode=HSE-External-Oscillator
PH0-OSC_IN\ (PH0).Signal=RCC_OSC_IN
PH1-OSC_OUT\ (PH1).Mode=HSE-External-Oscillator
PH1-OSC_OUT\ (PH1).Signal=RCC_OSC_OUT
RCC.SYSCLKFreq_VALUE=64000000
board=custom

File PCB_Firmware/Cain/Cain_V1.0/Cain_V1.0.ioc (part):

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Mcu.Name=STM32F105R(8-B-C)Tx
Mcu.Package=LQFP64
Mcu.UserName=STM32F105RBTx
PA13.Mode=Trace_Asynchronous_SW
PA13.Signal=SYS_JTMS-SWDIO
PA14.Mode=Trace_Asynchronous_SW
PA14.Signal=SYS_JTCK-SWCLK
PA6.GPIOParameters=GPIO_Label
PA6.GPIO_Label=PRESSURE
PA6.Signal=ADCx_IN6
PA8.GPIOParameters=GPIO_Label
PA8.GPIO_Label=BUTTON
PA8.Signal=GPIO_Input
PB1.GPIOParameters=GPIO_Label
PB1.GPIO_Label=CURRENT
PB1.Signal=ADCx_IN9
PB10.Mode=I2C
PB10.Signal=I2C2_SCL
PB11.Mode=I2C
PB11.Signal=I2C2_SDA
PB12.Mode=CAN_Activate
PB12.Signal=CAN2_RX
PB13.Mode=CAN_Activate
PB13.Signal=CAN2_TX
PB3.Mode=Trace_Asynchronous_SW
PB3.Signal=SYS_TRACESWO
PB6.GPIOParameters=PinState,GPIO_Label
PB6.GPIO_Label=LED_GREEN
PB6.PinState=GPIO_PIN_SET
PB6.Signal=GPIO_Output
PB8.GPIOParameters=PinState,GPIO_Label
PB8.GPIO_Label=LED_BLUE
PB8.PinState=GPIO_PIN_SET
PB8.Signal=GPIO_Output
PC10.Mode=Asynchronous
PC10.Signal=UART4_TX
PC11.Mode=Asynchronous
PC11.Signal=UART4_RX
PC13-TAMPER-RTC.GPIOParameters=PinState,GPIO_Label
PC13-TAMPER-RTC.GPIO_Label=LED_RED
PC13-TAMPER-RTC.PinState=GPIO_PIN_SET
PC13-TAMPER-RTC.Signal=GPIO_Output
PC14-OSC32_IN.GPIOParameters=GPIO_Label
PC14-OSC32_IN.GPIO_Label=TEST_LED
PC14-OSC32_IN.Signal=GPIO_Output
PC8.GPIOParameters=GPIO_Label
PC8.GPIO_Label=SOLENOID
PC8.Signal=GPIO_Output
PD0-OSC_IN.Mode=HSE-External-Oscillator
PD0-OSC_IN.Signal=RCC_OSC_IN
PD1-OSC_OUT.Mode=HSE-External-Oscillator
PD1-OSC_OUT.Signal=RCC_OSC_OUT
PD2.GPIOParameters=GPIO_Label
PD2.GPIO_Label=BOOT1
PD2.Signal=GPIO_Input
RCC.SYSCLKFreq_VALUE=8000000
board=custom

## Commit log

2025-06-25 Added title block template
2025-06-27 Beginnings of an interconnect
2025-07-02 Cain Board V1.0
2025-07-07 Electrical interconnect stuff
2025-07-08 File dump
2025-07-28 Update w new boards/firmware
